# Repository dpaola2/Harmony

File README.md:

# Offline MP3 Player (Harmony2)

Hardware-agnostic MP3 player core with a PC simulator and ESP32 targets. See `docs/README.md` for the doc map; hardware bring-up for Prototype 1 is in `hardware/prototype1/README.md`.

## Current Mark-6 build

The active player uses native ESP-IDF firmware on the Adafruit ESP32 Feather V2. The Python/MicroPython architecture below is retained historical context.

- [Feather bench firmware and instructions](firmware/mark-6/feather-player-bench/README.md)
- [Native UI and renderer](firmware/mark-6/feather-carrier/main/)
- [UI requirements and completion status](docs/Harmony-player-ui-requirements.md)
- [Desktop UI prototype](platforms/pc/ui/README.md)
- [Preserved Mark-7 visual reference](docs/mark-7-design-reference.md)
- [Changelog](CHANGELOG.md)

## Architecture & Goals
- Core app logic in Python, shared by PC simulator and MicroPython on ESP32.
- iPod-style UI: Library → Now Playing → Settings with tactile buttons (no touch).
- Portable storage (SD) and Bluetooth audio on hardware targets; PC sim for fast iteration.
- More context: `PROJECT_OVERVIEW.md` (goals/constraints) and `PLAN.md` (roadmap).

## Development
- **Environment (macOS)**:
  - Install Homebrew if missing: `/bin/bash -c "$(curl -fsSL https://raw.githubusercontent.com/Homebrew/install/HEAD/install.sh)"`.
  - Python: `brew install python` (or `pyenv` if you prefer pinned versions).
  - Recommended tooling: `pipx install uv` (or `pip install uv` in a venv); `pipx ensurepath`.
  - Create venv: `python -m venv .venv && source .venv/bin/activate`.
  - Install dev deps: `python -m pip install --upgrade pip uv pytest`.

- **Run PC simulator** (console UI):
  ```bash
  source .venv/bin/activate
  python -m platforms.pc.main_pc [--music-dir /path/to/Artist/Album/Track.ext]
  ```
  Controls: `w/s` up/down, `a` left, `d` right, `space`/Enter select, `p` play/pause, `b` or `q` back, `x` quit, `+`/`=` volume up, `-` volume down. Defaults to an in-memory demo library.

- **Tests**:
  ```bash
  source .venv/bin/activate
  pytest
  ```
  (Targets `core/` behavior.)

- **ESP32 Prototype 1 upload (demo UI, no buttons required)**:
  - See `hardware/prototype1/README.md` for wiring and flashing details.
  - Convenience script from repo root:
    ```bash
    scripts/upload_proto1_demo.sh /dev/tty.usbmodem*   # adjust port as needed
    ```
    It copies `core/`, `platforms/esp32/*.py`, and `main_esp32.py` to the board and keeps `main.py` as entrypoint.

## Repo structure
- `core/` hardware-agnostic logic and models
- `platforms/pc/` PC simulator (console screen, keyboard input, audio backend)
- `platforms/esp32/` ESP32 adapters (screen, buttons, audio)
- `hardware/` wiring/board notes (prototype phases)
- `enclosure/` mechanical notes
- `tests/` pytest cases for `core/`

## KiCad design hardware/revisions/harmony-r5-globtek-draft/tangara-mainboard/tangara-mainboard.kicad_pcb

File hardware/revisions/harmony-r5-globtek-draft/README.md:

# Harmony R5 GlobTek draft

U10 changed to MCP73871-1CCI/ML in schematic and PCB MPN property. Routed geometry and connectivity unchanged from R4. Local integration draft; not submitted or released. Temperature-sensor qualification remains open. See ../../procurement/globtek-integration/README.md.

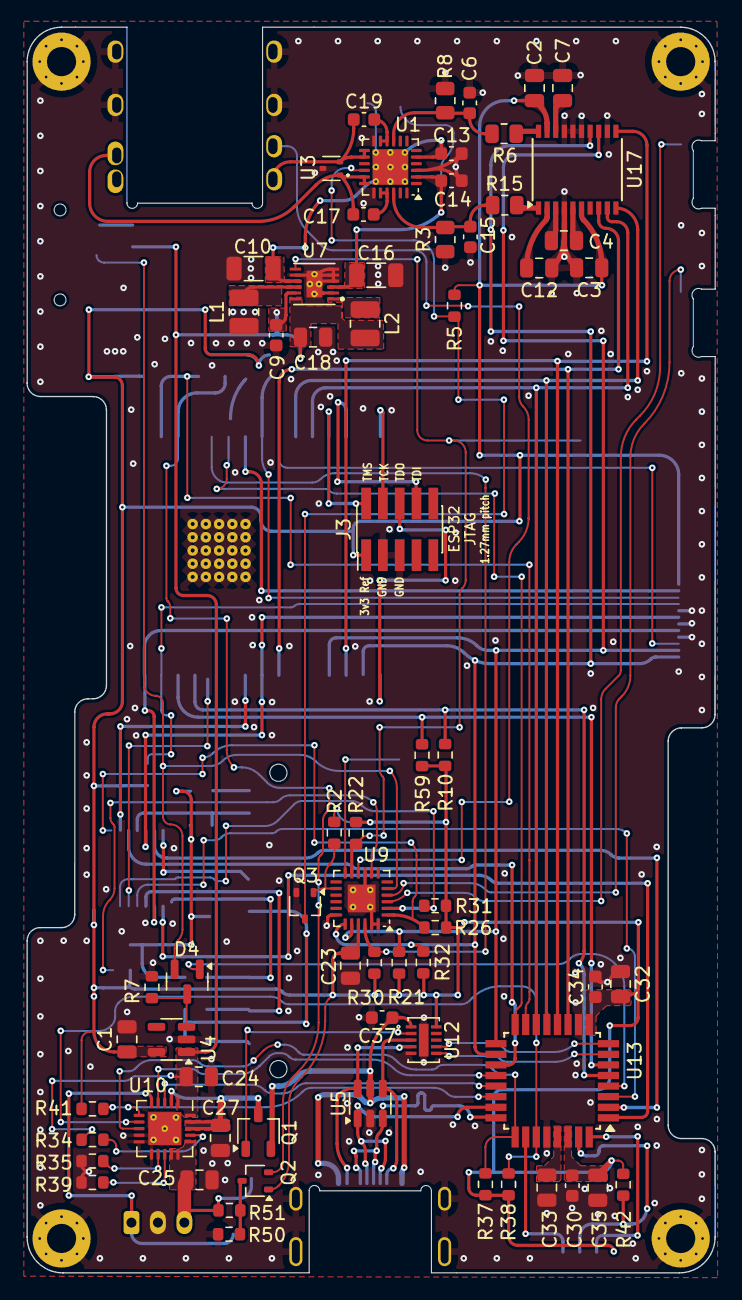
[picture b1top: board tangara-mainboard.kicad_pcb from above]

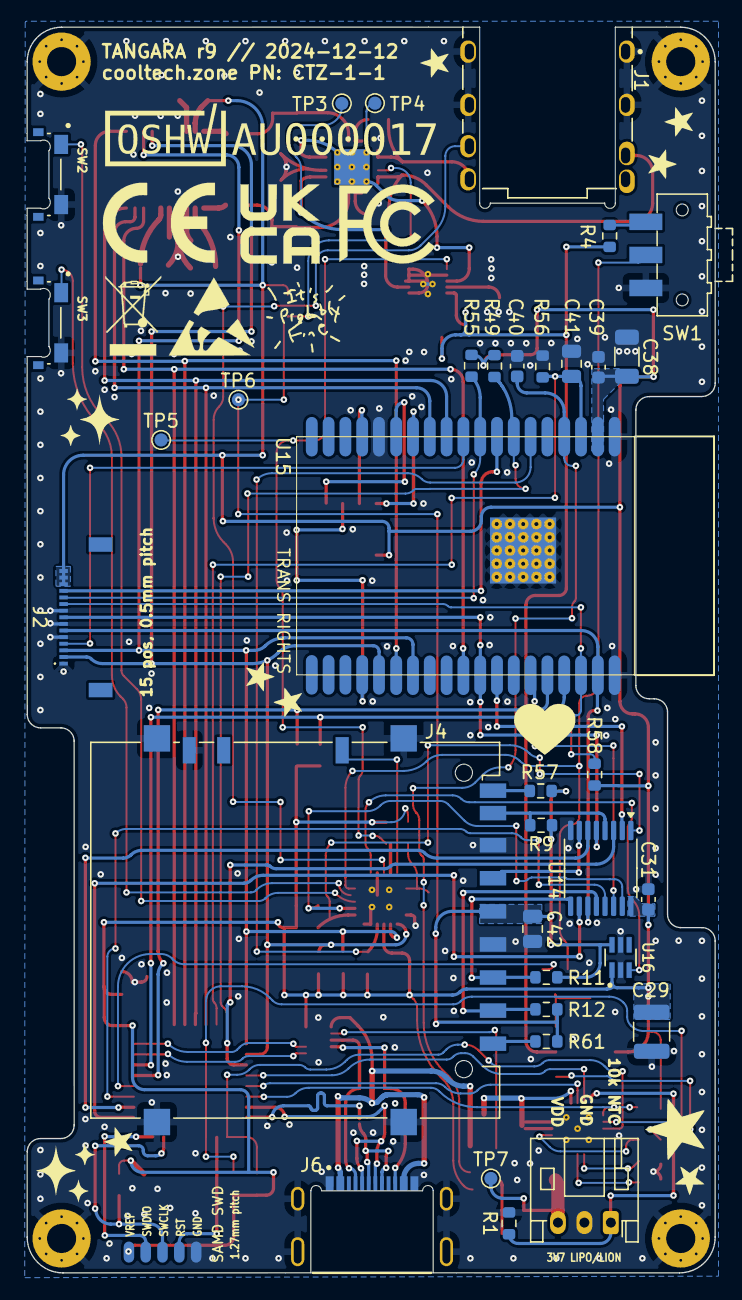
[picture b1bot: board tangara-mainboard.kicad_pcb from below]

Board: 4 copper layers, 52.0 x 94.2 mm, 106 parts (35 on the bottom side), 92 nets.

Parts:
C1, C2, C3, C7, C18, C24, C25, C27, C32, C35, C42: 10μF; C_0805_2012Metric
C4, C12, C23, C33, C41: 1μF; C_0805_2012Metric
C6, C15: 2700pF; C_0603_1608Metric
C9, C13, C14, C30, C31, C34, C37, C39, C40: 0.1μF; C_0603_1608Metric
C10, C16, C38: 22μF; C_1206_3216Metric
C17, C19: 100pF; C_0603_1608Metric
C29: 100uF; C_1210_3225Metric
D4: BAT54C; SOT-23
H1, H2, H3, H4: MountingHole; MountingHole_2.2mm_M2_Pad_Via2
J1: SJ-3506-SMT; CUI_SJ-3506-SMT
J2: FP Connector; G-Switch GT-F0509SR15-15SMT01
J3: JTAG; PinHeader_2x05_P1.27mm_Vertical_SMD
J4: SD_Card; SD_Hirose_DM1AA_SF_PEJ82
J5: SWD; SAMDSWD
J6: USB; GCT_USB4510-03-1-A_REVA
J7: Battery; JST_PH_S3B-PH-K_1x03_P2.00mm_Horizontal
L1, L2: 4.7μH; L_1008_2520Metric
Q1: PMV48XPA2R; TSOT-23
Q2, Q3: PJC138K; SOT-323_SC-70
R1, R2, R4, R5, R9, R10, R11, R12, R21, R22, R26, R30, R31, R32, R34, R35, R37, R38, R41, R49, R55, R57, R58, R59, R61: 10kΩ; R_0603_1608Metric
R3, R8: 2.2kΩ; R_0805_2012Metric
R6, R15: 560Ω; R_0805_2012Metric
R7, R50, R51, R56: 1MΩ; R_0603_1608Metric
R39, R42: 1kΩ; R_0603_1608Metric
SW1: SW_SPDT; SW_SPDT_CK-JS102011SAQN
SW2, SW3: SW_Push; SW_EVQ-P4HB3B
TP3: +5V; TestPoint_Pad_D1.0mm
TP4: -5V; TestPoint_Pad_D1.0mm
TP5: AMP_EN; TestPoint_Pad_D1.0mm
TP6: AMP_MUTE; TestPoint_Pad_D1.0mm
TP7: BAT; TestPoint_Pad_D1.0mm
U1: INA1620; QFN-24-1EP_4x4mm_P0.5mm_EP2.7x2.7mm_ThermalVias
U3: D5V0L2B3T-7; SOT-523
U4: TLV75533PDBV; SOT-23-5
U5: PE1605C4A6; SOT-23-6
U7: TPS65133; SON40P300X300X80-13N
U9: PCA8575; HVQFN-24-1EP_4x4mm_P0.5mm_EP2.1x2.1mm
U10: MCP73871; QFN-20-1EP_4x4mm_P0.5mm_EP2.5x2.5mm_ThermalVias2
U12: BD91N01NUX; BD91N01NUX-E2
U13: ATSAMD21E18A-AF; TQFP-32_7x7mm_P0.8mm
U14: 74CBTLV3257; TSSOP-16_4.4x5mm_P0.65mm
U15: ESP32-WROVER-E; ESP32-WROVER
U16: TPS22948; SOT65P210X110-6N
U17: WM8523; SSOP-20_4.4x6.5mm_P0.65mm

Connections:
3.5mm_DETECT: J1.4, U9.10 (IO1_0)
+3V3: C1.1, C2.2, C3.1, C23.1, C29.1, C30.1, C31.1, C32.2, C34.1, C35.2, C38.1, C39.1, J2.13, J2.14, J2.15, J3.1 (vRef), J5.1, Q2.1 (G), R2.2, R5.1, R10.1, R21.1, R22.2, R26.1, R30.1, R31.1, R32.1, R37.1, R38.1, R41.1, R42.1, R49.1, R55.1, R58.1, R59.1, U4.5 (OUT), U9.21 (VDD), U12.10 (VDD_IO), U13.9 (VDDANA), U13.30 (VDDIN), U14.16 (VCC), U15.2 (VDD), U16.1 (IN), U17.6 (LINEVDD), U17.19 (AVDD)
+5VA: C14.1, C16.1, TP3.1, U1.2 (V+), U7.3 (VPOS)
-5VA: C10.2, C13.1, TP4.1, U1.5 (V-), U1.25 (EP), U7.9 (VNEG)
/ESP_EN: C41.1, R56.2, U13.15 (PA14), U15.3 (EN)
/JTAG.TCK: J3.4 (TCK), U15.16 (JTAG.TCK)
/JTAG.TDI: J3.8 (TDI), U15.14 (JTAG.TDI)
/JTAG.TDO: J3.6 (TDO), U15.23 (JTAG.TDO)
/JTAG.TMS: J3.2 (TMS), U15.13 (JTAG.TMS)
/Power/NTC: J7.1, R1.1, U10.5 (THERM)
/Power/VBUS_SWITCHED: C27.1, Q1.3 (D), U10.2 (VPCC), U10.18 (IN), U10.19 (IN)
/SWD.RESET: J5.4, U13.26 (~RESET)
/SWD.SWCLK: J5.3, R42.2, U13.31 (SWCLK)
/SWD.SWDIO: J5.2, U13.32 (SWDIO)
/UART.ESP.RX: R10.2, U13.5 (PA04(SERCOM0.0)), U15.34 (UART.RX)
/UART.ESP.TX: R59.2, U13.6 (PA05(SERCOM0.1)), U15.35 (UART.TX)
/~SAMD_INT: R49.2, U13.16 (PA15), U15.7 (I35)
AMP_EN: R22.1, TP5.1, U7.7 (EN), U9.11 (IO1_1)
AMP_MUTE: Q3.3 (D), R5.2, TP6.1, U1.16 (EN)
BAT_LEVEL: C40.2, Q2.2 (S), U15.4 (ADC1_CH0/NOINT)
CHG_PROG: U10.4 (PROG2), U13.20 (PA19)
CHG_SEL: U10.3 (SEL), U13.21 (PA22)
CHG_STAT1: R37.2, U10.8 (STAT1/~LBO), U13.25 (PA27)
CHG_STAT2: R38.2, U10.7 (STAT2), U13.27 (PA28)
DAC.BCK: U13.13 (PA10(I2S/SCK)), U15.11 (I2S.BCK), U17.10 (BCLK)
DAC.DATA: U13.11 (PA08(I2S/SD)), U15.29 (I2S.DOUT), U17.8 (DACDAT)
DAC.LRCK: U13.14 (PA11(IS2/FS)), U15.12 (I2S.LRCK), U17.9 (LRCLK)
DAC.MCK: U13.12 (PA09(I2S/MCK)), U15.25 (BOOT/I2S.SCK), U17.11 (MCLK)
DISPLAY_DR: J2.11, R55.2, U15.9 (IO33)
DISPLAY_LED_EN: J2.12, U15.8 (IO32)
ESP_SPI.DISPLAY_CS: J2.10, R58.2, U15.36 (SPI.CS1)
ESP_SPI.PICO: J2.6, U14.11, U15.37 (SPI.PICO)
ESP_SPI.POCI: U14.2, U15.31 (SPI.POCI)
ESP_SPI.SCLK: J2.8, U14.5, U15.30 (SPI.CLK)
ESP_SPI.SD_CS: U14.14, U15.33 (SPI.CS0)
GND: C1.2, C2.1, C3.2, C6.1, C7.2, C9.2, C10.1, C12.1, C13.2, C14.2, C15.1, C16.2, C18.2, C23.2, C24.2, C25.2, C27.2, C29.2, C30.2, C31.2, C32.1, C33.1, C34.2, C35.1, C37.2, C38.2, C39.2, C40.1, C41.2, C42.2, H1.1, H2.1, H3.1, H4.1, J1.1, J1.5, J1.SH1, J1.SH2, J2.1, J2.5, J2.7, J2.9, J3.3 (GND), J3.5 (GND), J4.3 (VSS), J4.6 (VSS), J4.SH, J4.SW, J5.5, J6.A1_B12 (GND), J6.B1_A12 (GND), J6.S1 (SHELL_GND), J6.S2 (SHELL_GND), J6.S3 (SHELL_GND), J6.S4 (SHELL_GND), J7.2, L1.1, Q3.2 (S), R1.2, R3.1, R7.1, R8.1, R35.2, R39.2, R50.2, R56.1, SW1.1 (A), SW2.2, SW3.2, U1.3 (GND), U1.12, U1.19, U3.3, U4.2 (GND), U5.2 (GND), U7.2 (PGND), U7.4 (GND), U7.5 (AGND), U7.6 (GND), U7.8 (GND), U7.13 (EXP), U9.9 (VSS), U9.18 (A0), U9.23 (A1), U9.24 (A2), U9.25 (EP), U10.9 (~TE), U10.10 (V_{SS}), U10.11 (V_{SS}), U10.21 (V_{SS}), U12.5 (GND), U12.11 (EP), U13.10 (GND), U13.28 (GND), U14.8 (GND), U15.1 (GND), U15.15 (GND), U15.38 (GND), U15.39 (GND), U16.2 (GND), U16.5 (FLT), U17.4 (LINEGND), U17.12 (SDOUT/DEEMPH), U17.15 ({~CS}/{~MUTE}), U17.16 (CIFMODE), U17.17 (AGND)
I2C.SCL: J2.2, R26.2, U9.19 (SCL), U13.18 (PA17(SERCOM3.1)), U15.24 (I2C.SCL), U17.14 (SCLK)
I2C.SDA: J2.3, R21.2, U9.20 (SDA), U13.17 (PA16(SERCOM3.0)), U15.26 (I2C.SDA), U17.13 (SDA)
KEY_LOCK: D4.2, SW1.2 (B), U9.5 (IO0_4)
KEY_VOL_DOWN: SW3.1, U9.4 (IO0_3)
KEY_VOL_UP: SW2.1, U9.3 (IO0_2)
unnamed: C17.2, J1.2, U1.17, U1.18, U3.1
unnamed: C19.2, J1.3, U1.13, U1.14, U3.2
unnamed: J4.1 (CD/DAT3), R12.2, U14.12
unnamed: J4.5 (CLK), U14.7
unnamed: J4.2 (CMD), R11.2, U14.9
unnamed: J4.7 (DAT0), R9.2, U14.4
unnamed: J4.8 (DAT1), R57.2
unnamed: J4.9 (DAT2), R61.2
unnamed: C42.1, J4.4 (VDD), R9.1, R11.1, R12.1, R57.1, R61.1, U16.6 (OUT)
unnamed: J6.A5 (CC1), U5.4 (IO3), U12.3 (CC1)
unnamed: J6.B5 (CC2), U5.6 (IO5), U12.4 (CC2)
unnamed: C25.1, J7.3, R51.1, TP7.1, U10.14 (V_{BAT}), U10.15 (V_{BAT}), U10.16 (V_{BAT_SENSE})
unnamed: Q1.1 (G), U12.2 (SWDRV)
unnamed: Q2.3 (D), R50.1, R51.2
unnamed: Q3.1 (G), R2.1, U9.14 (IO1_4)
unnamed: R4.1, SW1.3 (C)
unnamed: C15.2, R3.2, R15.2, U1.22 (+)
unnamed: C17.1, U1.20, U1.21 (-)
unnamed: C6.2, R6.2, R8.2, U1.9 (+)
unnamed: C19.1, U1.10 (-), U1.11
unnamed: D4.3, R7.2, U4.3 (EN)
unnamed: L1.2, U7.10 (SWN)
unnamed: L2.1, U7.1 (SWP)
unnamed: R34.2, U10.17 (CE)
unnamed: R39.1, U10.13 (PROG1)
unnamed: R35.1, U10.12 (PROG3)
unnamed: C33.2, U13.29 (VDDCORE)
unnamed: R32.2, U9.1 (IO0_0), U14.1 (S)
unnamed: R31.2, U9.2 (IO0_1), U14.15 (~OE)
unnamed: C4.1, U17.5 (CPCA)
unnamed: C4.2, U17.3 (CPCB)
unnamed: C12.2, U17.2 (CPVOUTN)
unnamed: R15.1, U17.1 (LINEVOUTL)
unnamed: R6.1, U17.20 (LINEVOUTR)
unnamed: C7.1, U17.18 (VMID)
SAMD_SPI.CS: U13.3 (PA02), U14.13
SAMD_SPI.PICO: U13.1 (PA00(SERCOM1.0)), U14.10
SAMD_SPI.POCI: U13.19 (PA18(SERCOM1.2)), U14.3
SAMD_SPI.SCLK: U13.2 (PA01(SERCOM1.1)), U14.6
SD_CD: J4.CP, U9.12 (IO1_2)
SYS_POWER: C9.1, C18.1, C24.1, L2.2, R4.2, R34.1, U4.1 (IN), U7.11 (AVIN), U7.12 (PVIN), U10.1 (OUT), U10.20 (OUT)
SYS_PWR_EN_SAMD: D4.1, U13.4 (PA03)
USB.DN: J6.A7 (DN), J6.B7 (DN), U5.1 (IO1), U13.23 (USB.DM)
USB.DP: J6.A6 (DP), J6.B6 (DP), U5.3 (IO2), U13.24 (USB.DP)
USB_TCC0: U12.7 (TCC0), U13.8 (PA07)
USB_TCC1: U12.6 (TCC1), U13.7 (PA06)
VBUS: C37.1, J6.A4_B9 (VBUS), J6.B4_A9 (VBUS), Q1.2 (S), U5.5 (IO4), U12.1 (VBUS)
~CHG_PWR_OK: R41.2, U10.6 (~PG), U13.22 (PA23)
~GPIO_INT: R30.2, U9.22 (~INT), U15.6 (I34)
~SD_VDD_EN: U9.8 (IO0_7), U16.3 (ON)
~TOUCH_INT: J2.4, U15.10 (IO25)

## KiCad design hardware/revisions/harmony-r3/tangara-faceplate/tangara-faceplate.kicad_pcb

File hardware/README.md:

# Hardware Notes

## Prototypes
- Prototype 1: ESP32-S3-WROOM DevKitC-1 v1.1, SD SPI, ST7789V2 (1.69", 240x280), basic buttons, USB power. No audio/A2DP (S3 WROOM lacks classic BT); focus on UI/SD/display.
- Prototype 2: ESP32-WROVER DevKitC (PSRAM, classic BT) for audio/A2DP; SD SPI, ST7789 (2.0–2.4"), rotary encoder + buttons, optional I2S DAC/amp; USB or LiPo/TP4056 later.

## Volume Input Options
- Buttons: dedicated volume up/down buttons produce relative events; core clamps 0–100 and calls `set_volume`.
- Encoder-as-volume: use a second rotary (or mode switch) to emit relative steps; map to the same core events.
- Absolute knob (potentiometer): yields an analog value; platform adapter should translate ADC reading to a clamped 0–100 and push into core via `set_volume` (core supports absolute level set).

## Power System
- Battery: LiPo 1000–2000 mAh flat cell.
- Charging: TP4056 (USB-C variant) for LiPo charging.
- Regulation: ESP32 dev board regulator or MT3608 step-up if 5V needed for peripherals.
- Power switch: SPDT slide/lockable on/off.
- Optional: battery voltage sensing via ADC for future battery UI; plan GPIO and resistor divider.

## Notes/Next Steps
- Wiring: document GPIO mapping for encoder, buttons, SD (SPI), display (SPI), and optional I2S pins.
- Bluetooth A2DP: confirm ESP32 MicroPython support vs ESP-IDF shim; may need C-extension for stable source mode.
- Settings persistence: volume, last track, etc., stored in flash/SD (JSON) on device; core ready once adapters persist/load.

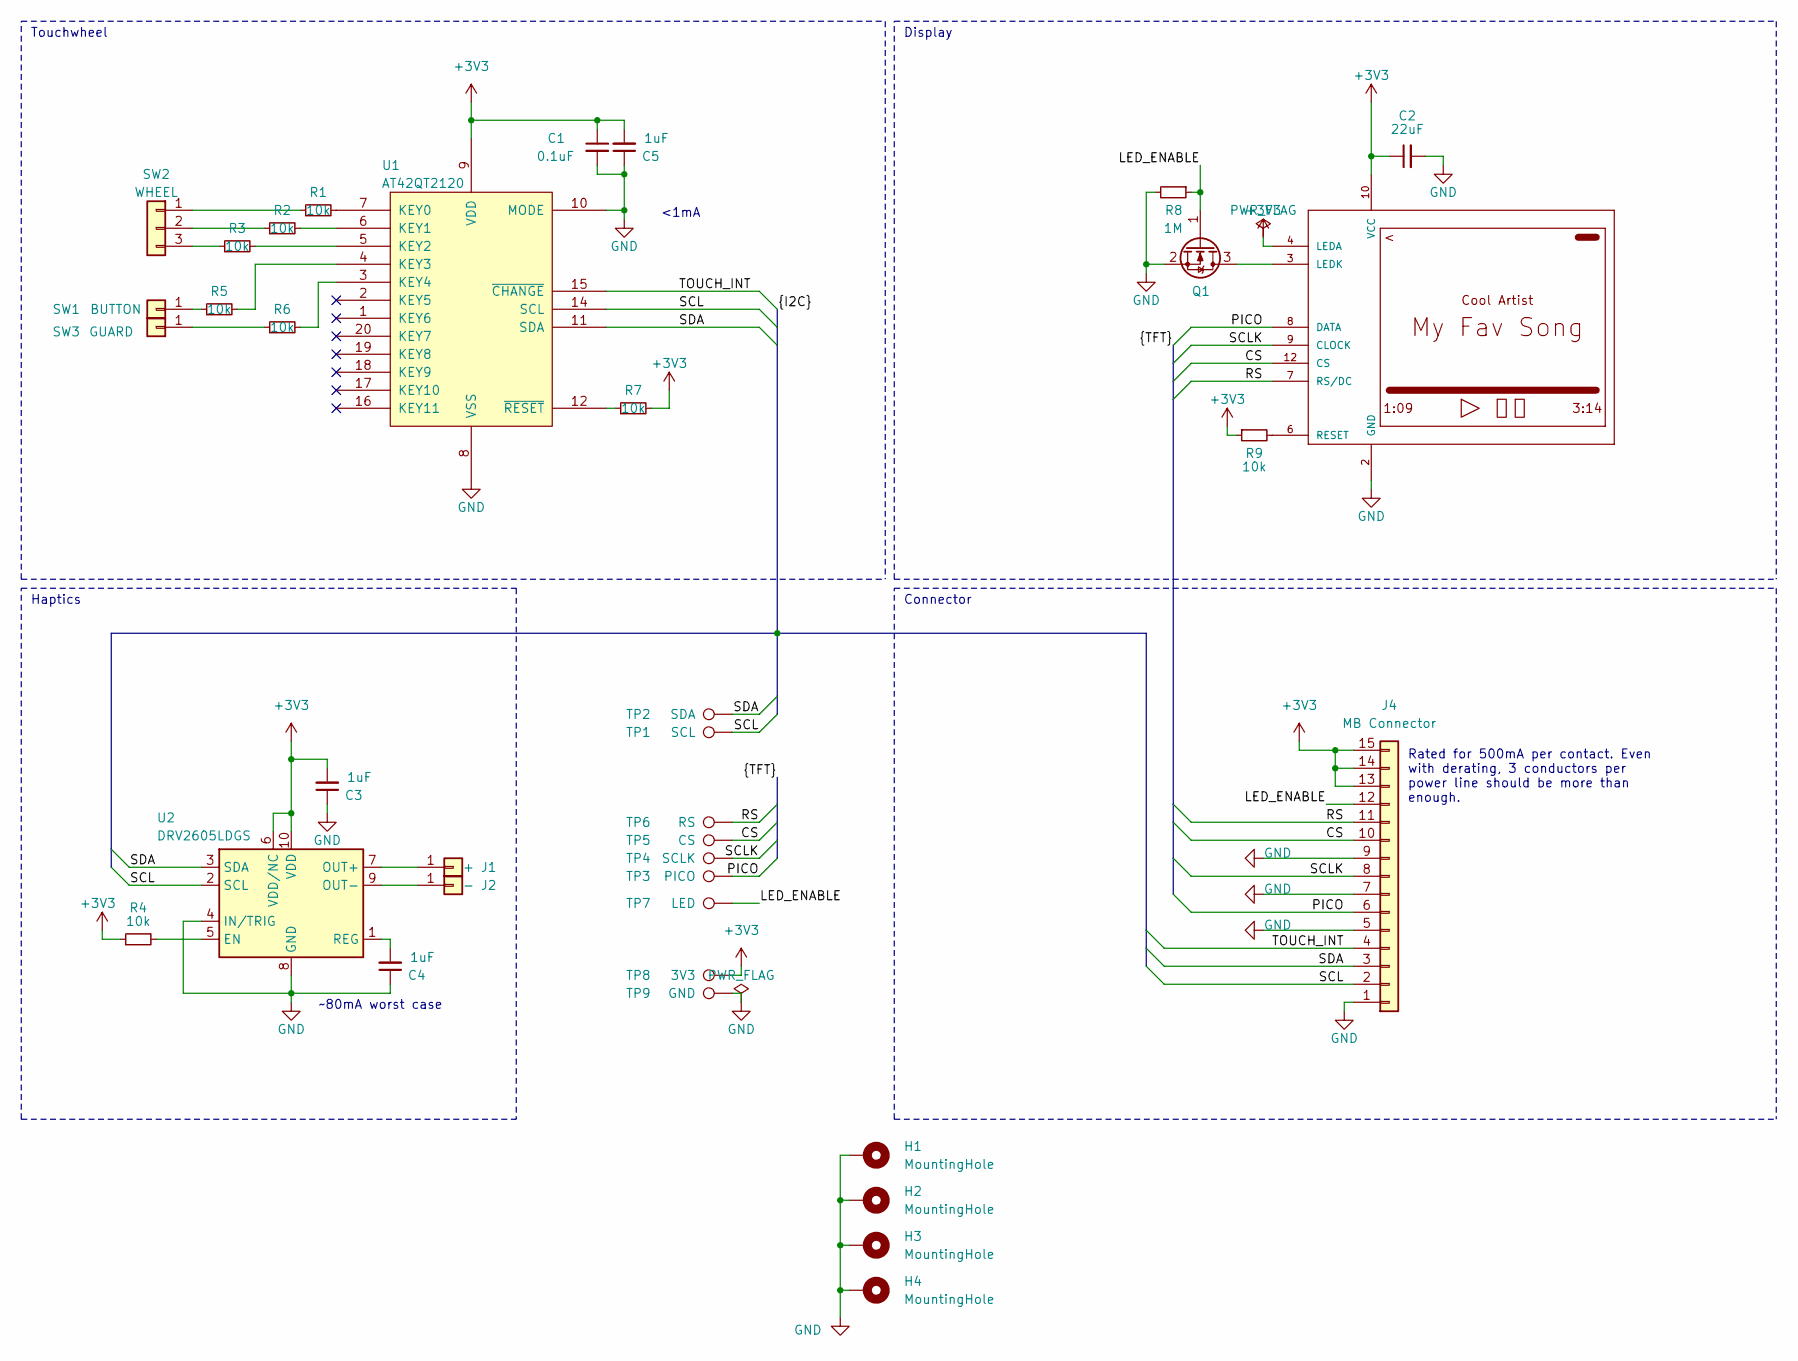
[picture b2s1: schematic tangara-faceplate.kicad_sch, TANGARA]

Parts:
C1: 0.1uF; C_0603_1608Metric; MPN GCM188R71C104KA37J
C2: 22uF; C_1206_3216Metric; MPN GRM319R61C226KE15D
C3, C4, C5: 1uF; C_0805_2012Metric; MPN GRM216R61C105KA88D
H1, H2, H3, H4: MountingHole; MountingHole_2.2mm_M2_Pad_Via
J1: +; TestPoint_Pad_D1.5mm
J2: -; TestPoint_Pad_D1.5mm
J4: MB Connector; G-Switch GT-F0509SR15-15SMT01; MPN GT-F0509SR15-15SMT01
LCD1: JD-T1800
Q1: PJC138K; SOT-323_SC-70; MPN PJC138K_R1_00001
R1, R2, R3, R4, R5, R6, R7, R9: 10k; R_0603_1608Metric; MPN AC0603JR-0710KL
R8: 1M; R_0603_1608Metric; MPN AC0603FR-131ML
SW1: BUTTON; qtouch-button
SW2: WHEEL; qtouch-wheel
SW3: GUARD; qtouch-guard
TP1: SCL; TestPoint_Pad_D1.0mm
TP2: SDA; TestPoint_Pad_D1.0mm
TP3: PICO; TestPoint_Pad_D1.0mm
TP4: SCLK; TestPoint_Pad_D1.0mm
TP5: CS; TestPoint_Pad_D1.0mm
TP6: RS; TestPoint_Pad_D1.0mm
TP7: LED; TestPoint_Pad_D1.0mm
TP8: 3V3; TestPoint_Pad_D1.0mm
TP9: GND; TestPoint_Pad_D1.0mm
U1: AT42QT2120; VQFN-20-1EP_3x3mm_P0.45mm_EP1.55x1.55mm; MPN AT42QT2120-MMH
U2: DRV2605LDGS; VSSOP-10_3x3mm_P0.5mm; MPN DRV2605LDGST

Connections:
+3V3: C1.1, C2.1, C3.2, C5.2, J4.13, J4.14, J4.15, LCD1.4 (LEDA), LCD1.10 (VCC), LCD1.11 (VCC2), R4.1, R7.2, R9.1, TP8.1, U1.9 (VDD), U2.6 (VDD/NC), U2.10 (VDD)
/CS: J4.10, LCD1.12 (CS), TP5.1
/LED_ENABLE: J4.12, Q1.1 (G), R8.1, TP7.1
/PICO: J4.6, LCD1.8 (DATA), TP3.1
/RS: J4.11, LCD1.7 (RS/DC), TP6.1
/SCL: J4.2, TP1.1, U1.14 (SCL), U2.2 (SCL)
/SCLK: J4.8, LCD1.9 (CLOCK), TP4.1
/SDA: J4.3, TP2.1, U1.11 (SDA), U2.3 (SDA)
/TOUCH_INT: J4.4, U1.15 (~CHANGE)
GND: C1.2, C2.2, C3.1, C4.1, C5.1, H1.1, H2.1, H3.1, H4.1, J4.1, J4.5, J4.7, J4.9, LCD1.2 (GND), LCD1.5 (GND1), LCD1.13 (GND2), Q1.2 (S), R8.2, TP9.1, U1.8 (VSS), U1.10 (MODE), U2.4 (IN/TRIG), U2.8 (GND)
unnamed: J1.1, U2.7 (OUT+)
unnamed: J2.1, U2.9 (OUT-)
unnamed: LCD1.3 (LEDK), Q1.3 (D)
unnamed: LCD1.6 (RESET), R9.2
unnamed: R5.1, SW1.1
unnamed: R1.1, SW2.1
unnamed: R2.1, SW2.2
unnamed: R3.1, SW2.3
unnamed: R6.1, SW3.1
unnamed: R1.2, U1.7 (KEY0)
unnamed: R2.2, U1.6 (KEY1)
unnamed: R3.2, U1.5 (KEY2)
unnamed: R5.2, U1.4 (KEY3)
unnamed: R6.2, U1.3 (KEY4)
unnamed: R7.1, U1.12 (~RESET)
unnamed: R4.2, U2.5 (EN)
unnamed: C4.2, U2.1 (REG)

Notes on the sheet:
Haptics
Touchwheel
~80mA worst case
Connector
Display
Rated for 500mA per contact. Even with derating, 3 conductors per power line should be more than enough.
<1mA

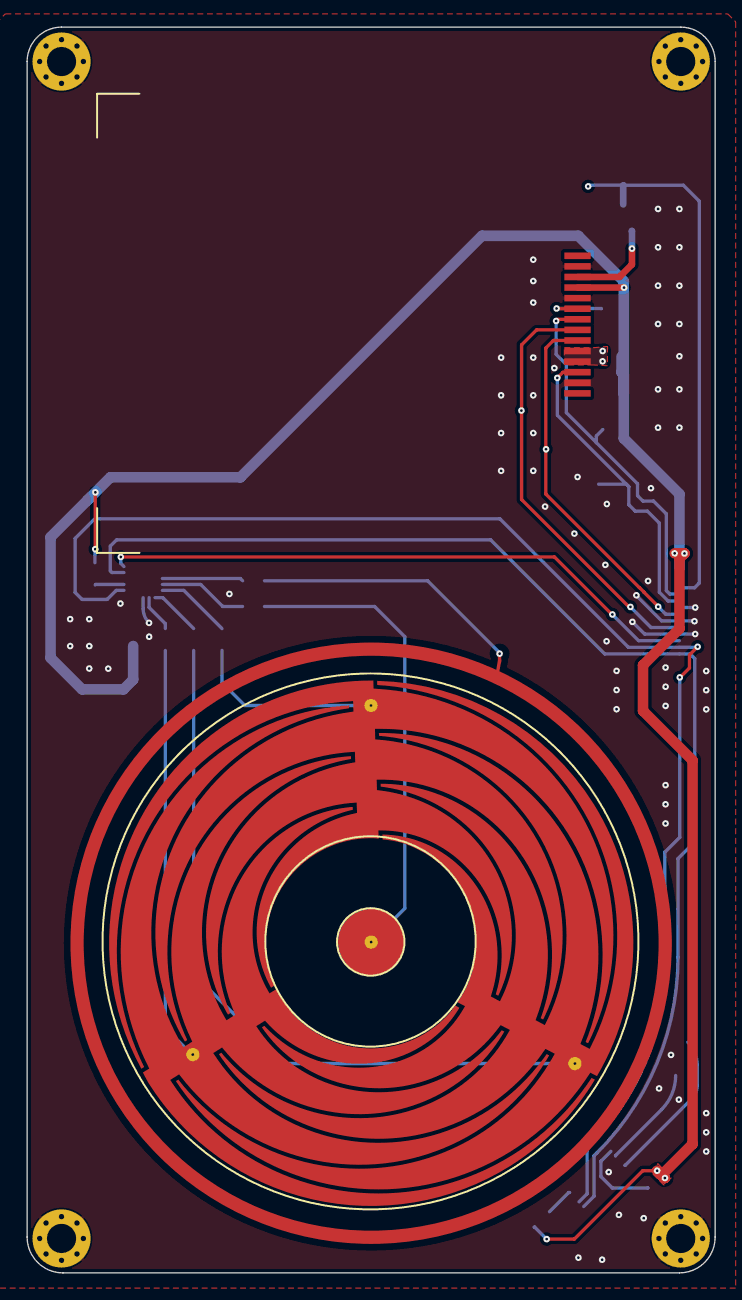
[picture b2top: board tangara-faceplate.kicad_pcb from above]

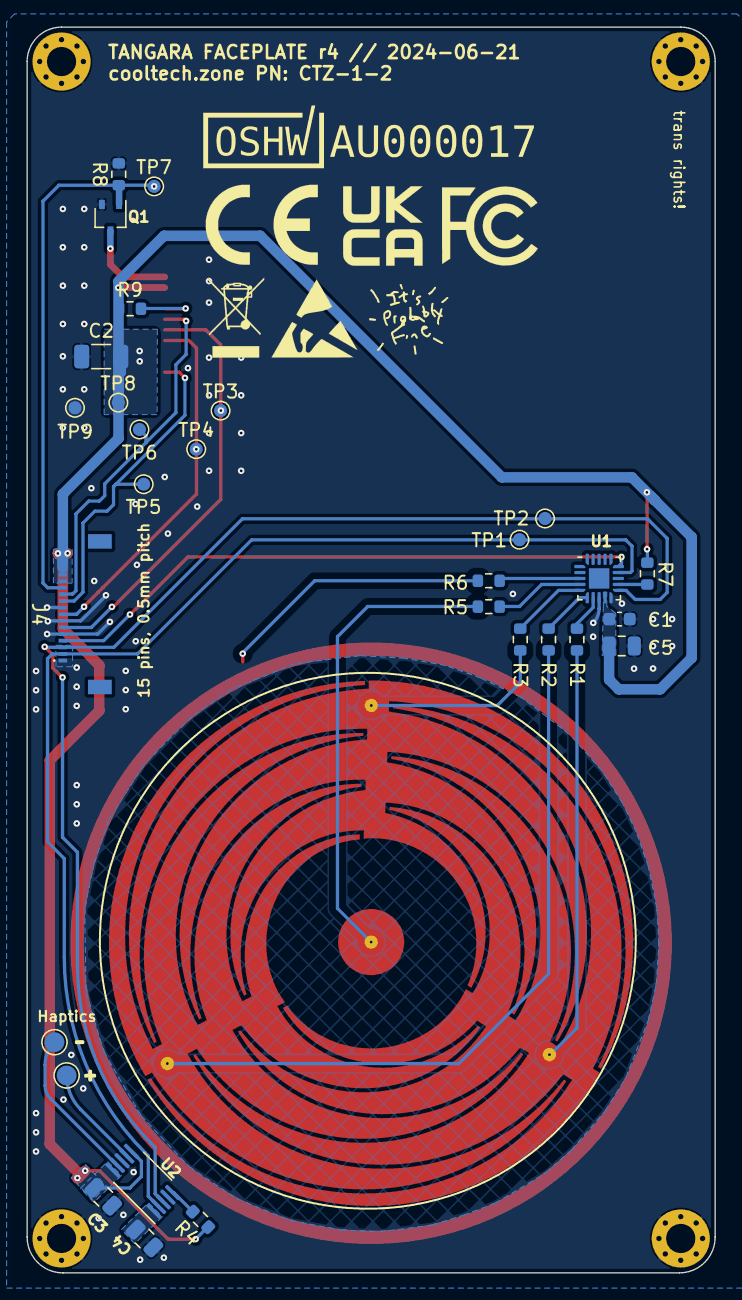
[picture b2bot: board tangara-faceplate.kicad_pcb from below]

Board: 2 copper layers, 52.0 x 94.2 mm, 39 parts (31 on the bottom side), 27 nets.

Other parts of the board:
kibuzzard-63E31E51: G***; kibuzzard-63E31E51
kibuzzard-63E31E57: G***; kibuzzard-63E31E57

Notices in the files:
hardware/revisions/harmony-r3/tangara-faceplate/tangara-faceplate.kicad_sch:
SPDX-License-Identifier: CERN-OHL-S-2.0
parts and their libraries:
Copyright 2021 Accelerated Designs. All rights reserved.
